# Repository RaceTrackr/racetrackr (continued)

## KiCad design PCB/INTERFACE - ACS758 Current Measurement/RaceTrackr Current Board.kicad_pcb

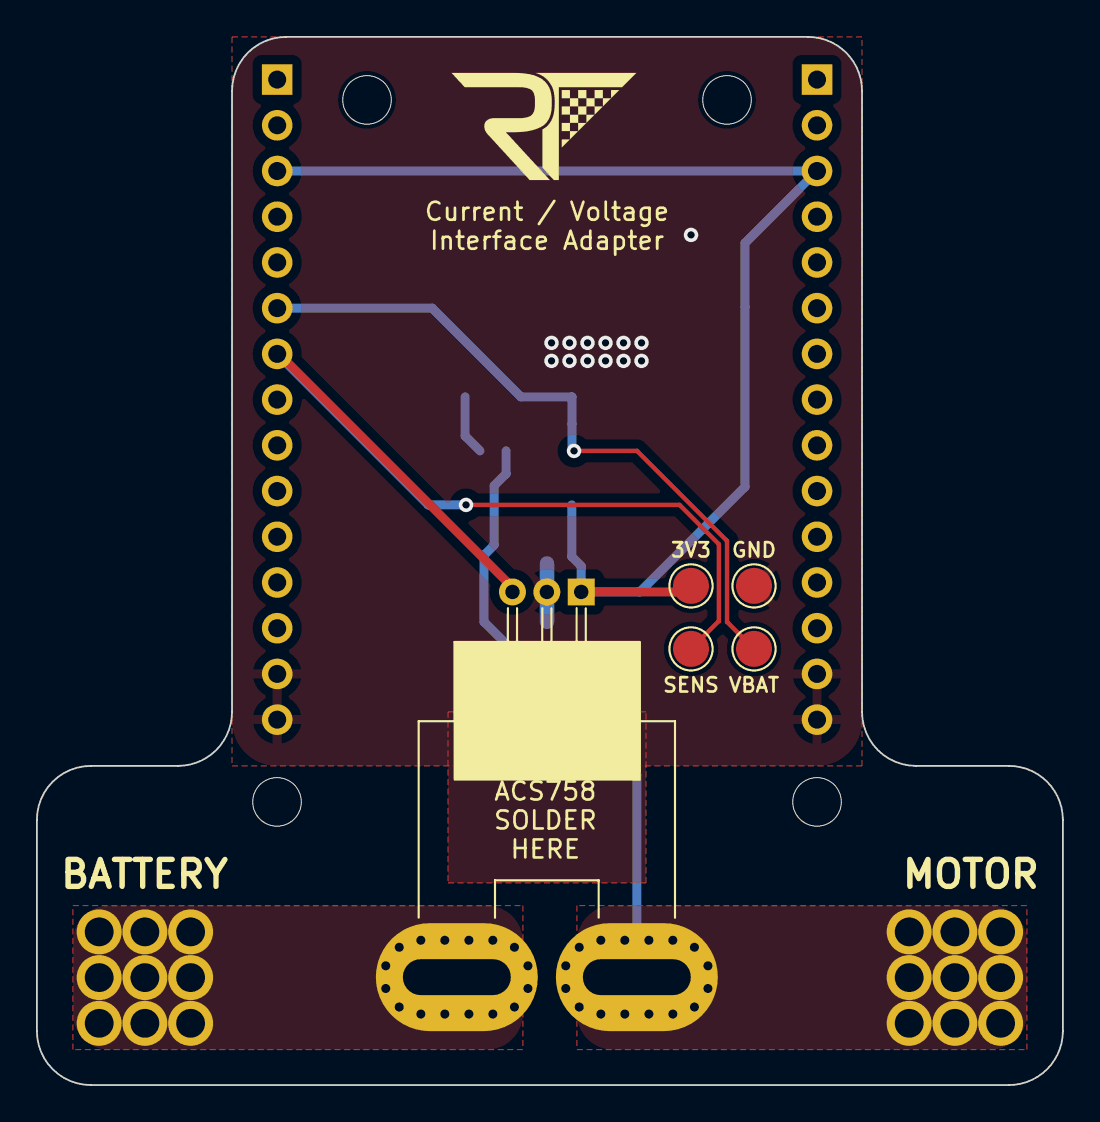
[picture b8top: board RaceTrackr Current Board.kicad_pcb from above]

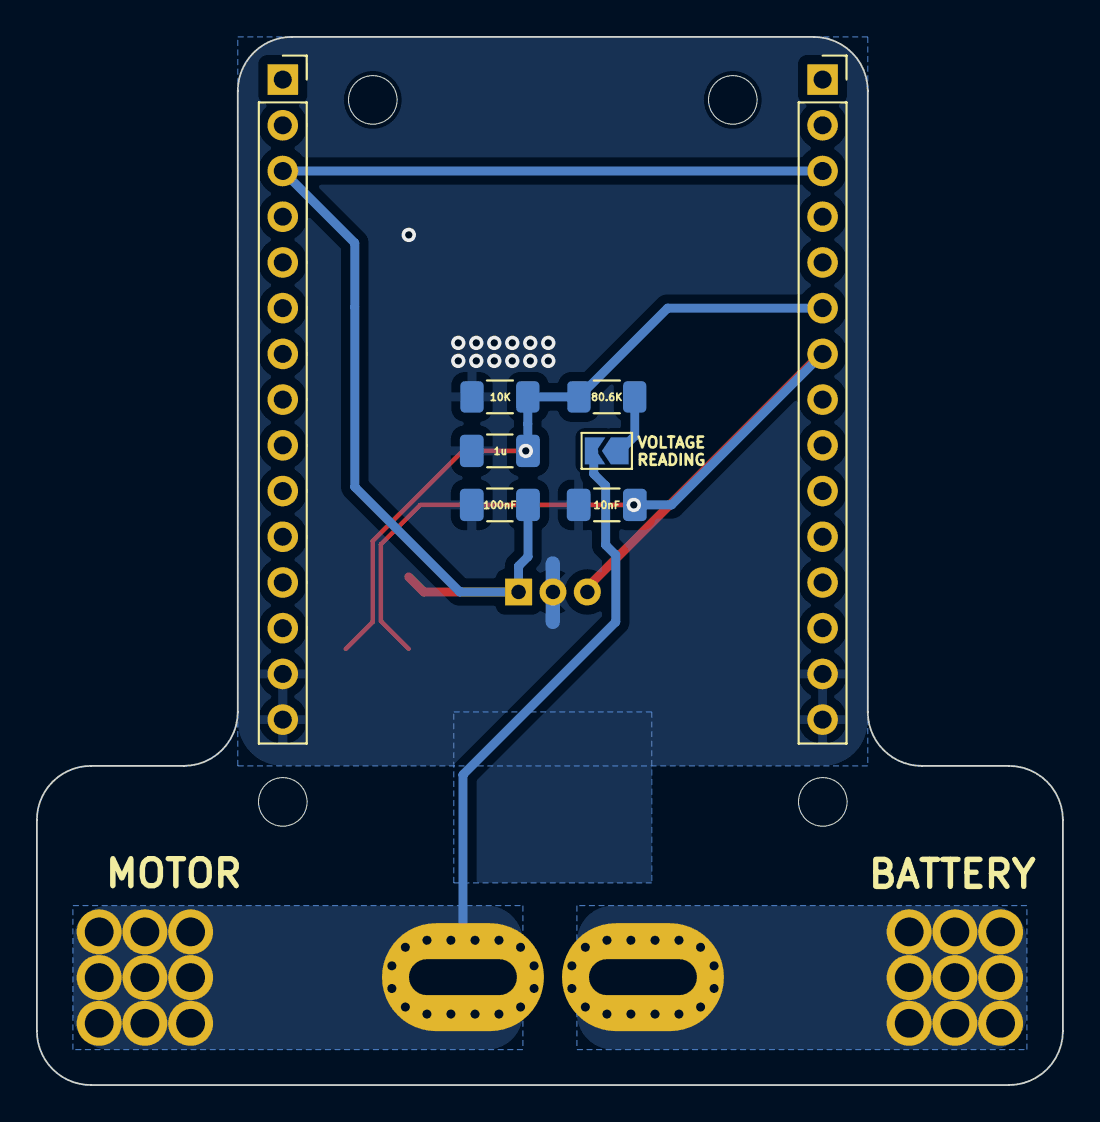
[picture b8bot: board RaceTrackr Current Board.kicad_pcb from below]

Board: 2 copper layers, 57.0 x 58.2 mm, 14 parts (8 on the bottom side), 7 nets.

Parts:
3V3: 3V3Test; TestPoint_Pad_D2.0mm
C1: 100nF; C_1206_3216Metric_Pad1.33x1.80mm_HandSolder
C2: 1u; C_1206_3216Metric_Pad1.33x1.80mm_HandSolder
C3: 10nF; C_1206_3216Metric_Pad1.33x1.80mm_HandSolder
GND: GNDTest; TestPoint_Pad_D2.0mm
IN1: BATT_IN; BoltFootprint
JP1: Jumper_2_Open; SolderJumper-2_P1.3mm_Open_TrianglePad1.0x1.5mm
OUT1: 24V_OUT; BoltFootprint
R1: 80.6K; R_1206_3216Metric_Pad1.30x1.75mm_HandSolder
R2: 10K; R_1206_3216Metric_Pad1.30x1.75mm_HandSolder
SENS: CurrentSense; TestPoint_Pad_D2.0mm
U1: ACS758xCB-100U-PFF; Allegro_CB_PFF
U2: RaceTrackr Interface Board Reference
VBAT: VBATTest; TestPoint_Pad_D2.0mm

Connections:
+3V3: 3V3.1, C1.1, U1.1 (VCC), U2.3 (3V3), U2.28 (3V3)
/24V_OUT: JP1.2 (B), OUT1.1, U1.5 (IP-)
/BATT_IN: IN1.1, U1.4 (IP+)
CURRENT_SENSE: C3.1, SENS.1, U1.3 (VIOUT), U2.7 (GPIO3)
GND: C1.2, C2.2, C3.2, GND.1, R2.2, U1.2 (GND), U2.14 (GND), U2.15 (GND), U2.16 (GND), U2.17 (GND)
unnamed: JP1.1 (A), R1.1
V_Bat: C2.1, R1.2, R2.1, U2.6 (GPIO2), VBAT.1

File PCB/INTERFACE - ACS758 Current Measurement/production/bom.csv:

Designator,Footprint,Quantity,Value,LCSC Part #
3V3,TestPoint_Pad_D2.0mm,1,3V3Test,
C1,1206,1,100nF,
C2,1206,1,1u,
C3,1206,1,10nF,
GND,TestPoint_Pad_D2.0mm,1,GNDTest,
IN1,BoltFootprint,1,BATT_IN,
JP1,SolderJumper-2_P1.3mm_Open_TrianglePad1.0x1.5mm,1,Jumper_2_Open,
OUT1,BoltFootprint,1,24V_OUT,
R1,1206,1,80.6K,
R2,1206,1,10K,
SENS,TestPoint_Pad_D2.0mm,1,CurrentSense,
U1,Allegro_CB_PFF,1,ACS758xCB-100U-PFF,
U2,RaceTrackr Interface Board Reference,1,~,
VBAT,TestPoint_Pad_D2.0mm,1,VBATTest,

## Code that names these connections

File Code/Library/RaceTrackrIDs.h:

#define ID_EMERGENCY_STOP 0x000
#define ID_DATA_PULSE 0x001
#define ID_RACE_START 0x002
#define ID_LAUNCH_CONTROL 0x003

#define ID_BRAKE_ON 0x004
#define ID_BRAKE_OFF 0x005
#define ID_HORN_ON 0x006
#define ID_HORN_OFF 0x007

#define ID_IGNITION_STATE 0x008
#define ID_MOTOR_PWM 0x009
#define ID_THROTTLE_RAW 0x00A
#define ID_THROTTLE_MODE 0x00B
#define ID_THROTTLE_PARAMETERS 0x00C
#define ID_MOTOR_VOLTAGE_CURRENT 0x00D
#define ID_TEMPERATURE 0x00E
#define ID_RPM 0x00F
#define ID_FAN 0x010

#define ID_DISPLAY_VOLTAGE_CURRENT 0x010
#define ID_DISPLAY_AMP_HOURS 0x011
#define ID_DISPLAY_MOTOR_INFO 0x012
#define ID_DISPLAY_TTE 0x013
#define ID_DISPLAY_DASHBOARD_BUTTON 0x014

#define ID_RADIO_PTT_ON 0x018
#define ID_RADIO_PTT_OFF 0x019
#define ID_ECHOOK_SCREEN_SWITCH 0x01A
#define ID_ECHOOK_LAUNCH 0x01B

#define ID_TELEMETRY_VOLTAGE_CURRENT 0x060
#define ID_TELEMETRY_MOTOR_RPM 0x061
#define ID_TELEMETRY_THROTTLE 0x062
#define ID_TELEMETRY_GPS_LOC 0x063
#define ID_TELEMETRY_GPS_INFO 0x064

typedef struct
{
    int id;
    const char *name;
    const char *description;
} CAN_ADDRESS;

#define NUMBER_CAN_IDS 12

const CAN_ADDRESS idEmergencyStop = {ID_EMERGENCY_STOP, "EMERGENCY", "Emergency Stop"};
const CAN_ADDRESS idDataPulse = {ID_DATA_PULSE, "DATAPULSE", "Data Pulse"};

const CAN_ADDRESS idBrakeOn = {ID_BRAKE_ON, "BRAKE ON", "Brake On"};
const CAN_ADDRESS idBrakeOff = {ID_BRAKE_OFF, "BRAKE OFF", "Brake Off"};
const CAN_ADDRESS idHornOn = {ID_HORN_ON, "HORN ON", "Horn On"};
const CAN_ADDRESS idHornOff = {ID_HORN_OFF, "HORN OFF", "Horn Off"};

const CAN_ADDRESS idIgnitionState = {ID_IGNITION_STATE, "IGNITION", "Ignition State"};
const CAN_ADDRESS idMotorPwm = {ID_MOTOR_PWM, "MOTOR PWM", "Motor PWM"};
const CAN_ADDRESS idThrottleRaw = {ID_THROTTLE_RAW, "THR READ", "Throttle Reading"};
const CAN_ADDRESS idThrottleMode = {ID_THROTTLE_MODE, "THR MODE", "Throttle Mode"};
const CAN_ADDRESS idThrottleParameters = {ID_THROTTLE_PARAMETERS, "THR PARAM", "Throttle Parameters"};
const CAN_ADDRESS idMotorVoltageCurrent = {ID_MOTOR_VOLTAGE_CURRENT, "VOLT/CURR", "Voltage / Current"};

const CAN_ADDRESS CAN_LOOKUP[NUMBER_CAN_IDS] = {
    idEmergencyStop,
    idDataPulse,
    idBrakeOn,
    idBrakeOff,
    idHornOn,
    idHornOff,
    idIgnitionState,
    idMotorPwm,
    idThrottleRaw,
    idThrottleMode,
    idThrottleParameters,
    idMotorVoltageCurrent};

const char ECHOOK_SPEED_ID = 's';
const char ECHOOK_MOTOR_ID = 'm';
const char ECHOOK_CURRENT_ID = 'i';
const char ECHOOK_VOLTAGE_ID = 'v';
const char ECHOOK_VOLTAGE_LOWER_ID = 'w';
const char ECHOOK_THROTTLE_INPUT_ID = 't';
const char ECHOOK_THROTTLE_ACTUAL_ID = 'd';
const char ECHOOK_TEMP1_ID = 'a';
const char ECHOOK_TEMP2_ID = 'b';
const char ECHOOK_TEMP3_ID = 'c';
const char ECHOOK_LAUNCH_MODE_ID = 'L';
const char ECHOOK_CYCLE_VIEW_ID = 'C';
const char ECHOOK_GEAR_RATIO_ID = 'r';
const char ECHOOK_BRAKE_PRESSED_ID = 'B';

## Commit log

2022-01-01 Uploaded logo files for use in applications
2022-08-28 Creation of RaceTrackr KiCad Library
    Symbols, footprints and 3D files for components used in KiCad projects
2022-09-02 Updated to include components used in eChook Wireless Adapter Board
    Updated to include components used in eChook Wireless Adapter Board
2022-09-02 eChook Wireless Adapter Board v1.0 [initial commit]
2022-09-18 Updated wireless board to V1.1
    Fixed unconnected ground plane error of V1.0 board.
2023-07-02 PCB Library Update
    Updated schematic library, footprints, and 3D models.
2023-07-02 First commit of RaceTrackr library
2023-07-02 Revert "PCB Library Update"
    This reverts commit 21be78e475dbc72d5667ee825550674702671899.
2024-02-16 Updated RaceTrackr code
2024-02-16 Deleted folder name ".." in Code/Library
    It had the exact copy of the entire Code/Library directory for some reason... so I just deleted it.
2024-02-16 Revert "Deleted folder name ".." in Code/Library"
    This reverts commit 26c52b9428086c4735f4b0afb187e6ca2c25a246.
2024-02-16 Updated git ignore file
2024-02-16 Added common types to .gitignore
2024-09-29 Add sendByte function
    Add ability to send a single byte message instead of having to construct a blank array each time.
2024-09-29 Waveshare 7 compatability
    Added ability to use Waveshare 7" ESP32 board.
